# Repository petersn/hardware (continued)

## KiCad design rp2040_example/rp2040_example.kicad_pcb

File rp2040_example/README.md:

RP2040 example board
====================

This board is enormously cribbed from the RP2040 example board, as described here: https://datasheets.raspberrypi.com/rp2040/hardware-design-with-rp2040.pdf

(The corresponding KiCad files are here: https://datasheets.raspberrypi.com/rp2040/Minimal-KiCAD.zip)

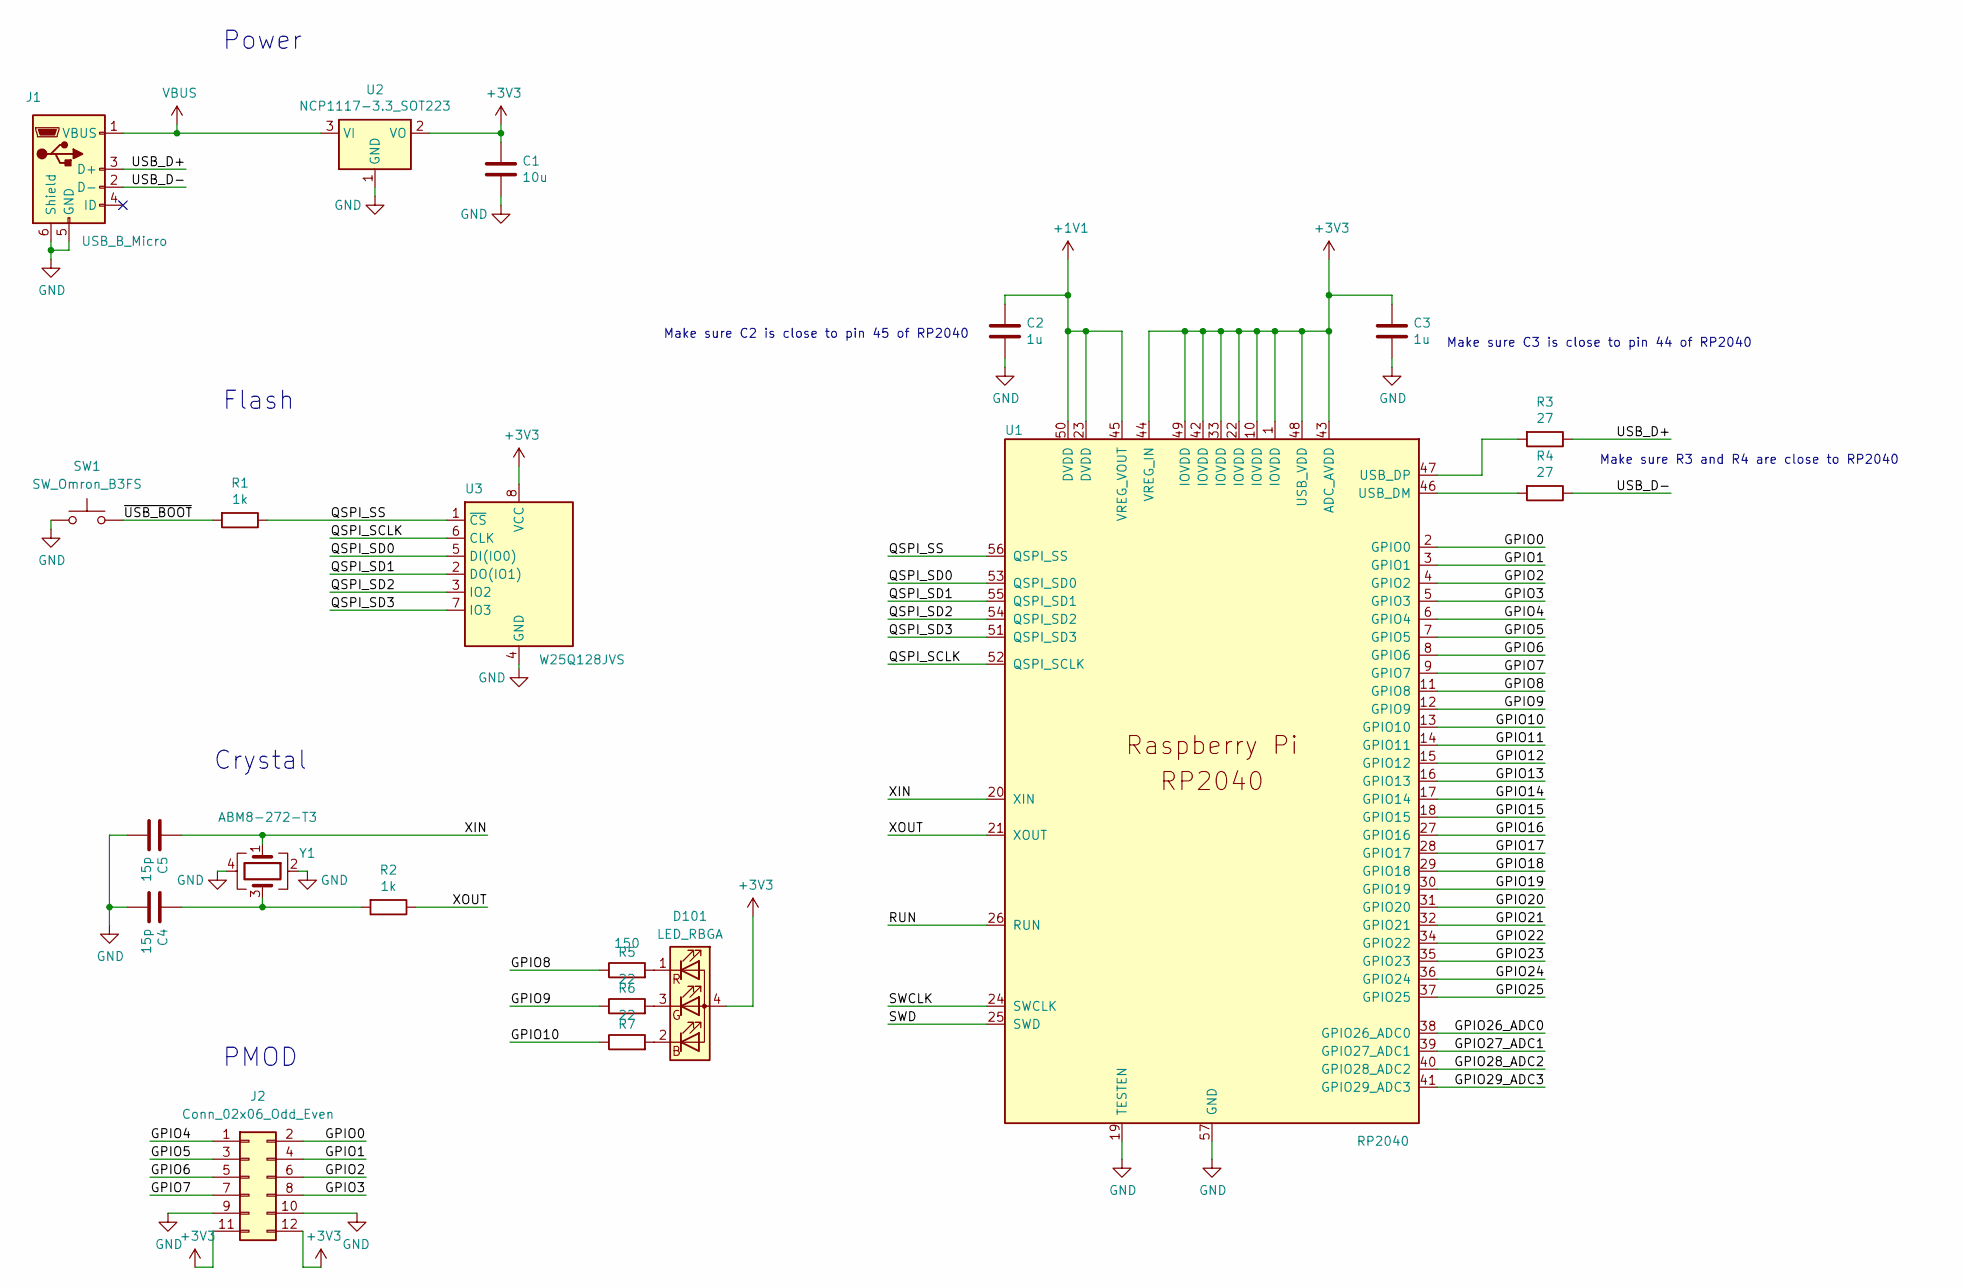
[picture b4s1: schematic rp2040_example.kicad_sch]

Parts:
C1: 10u; C_0805_2012Metric
C2, C3: 1u; C_0402_1005Metric
C4, C5: 15p; C_0402_1005Metric
D101: LED_RBGA; LED_LiteOn_LTST-C19HE1WT
J1: USB_B_Micro; USB_Micro-B_Amphenol_10103594-0001LF_Horizontal
J2: Conn_02x06_Odd_Even; PinHeader_2x06_P2.54mm_Vertical
R1, R2: 1k; R_0402_1005Metric
R3, R4: 27; R_0402_1005Metric
R5: 150; R_0402_1005Metric
R6, R7: 22; R_0402_1005Metric
SW1: SW_Omron_B3FS; SW_PUSH_6mm
U1: RP2040; QFN-56-1EP_7x7mm_P0.4mm_EP4x4mm_ThermalVias
U2: NCP1117-3.3_SOT223; SOT-223-3_TabPin2
U3: W25Q128JVS; SOIC-8_5.23x5.23mm_P1.27mm
Y1: ABM8-272-T3; Crystal_SMD_3225-4Pin_3.2x2.5mm

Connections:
+1V1: C2.1, U1.23 (DVDD), U1.45 (VREG_VOUT), U1.50 (DVDD)
+3V3: C1.1, C3.1, D101.4 (A), J2.11, J2.12, U1.1 (IOVDD), U1.10 (IOVDD), U1.22 (IOVDD), U1.33 (IOVDD), U1.42 (IOVDD), U1.43 (ADC_AVDD), U1.44 (VREG_IN), U1.48 (USB_VDD), U1.49 (IOVDD), U2.2 (VO), U3.8 (VCC)
/GPIO0: J2.2, U1.2 (GPIO0)
/GPIO1: J2.4, U1.3 (GPIO1)
/GPIO2: J2.6, U1.4 (GPIO2)
/GPIO3: J2.8, U1.5 (GPIO3)
/GPIO4: J2.1, U1.6 (GPIO4)
/GPIO5: J2.3, U1.7 (GPIO5)
/GPIO6: J2.5, U1.8 (GPIO6)
/GPIO7: J2.7, U1.9 (GPIO7)
/GPIO8: R5.1, U1.11 (GPIO8)
/GPIO9: R6.1, U1.12 (GPIO9)
/GPIO10: R7.1, U1.13 (GPIO10)
/GPIO11: U1.14 (GPIO11)
/GPIO12: U1.15 (GPIO12)
/GPIO13: U1.16 (GPIO13)
/GPIO14: U1.17 (GPIO14)
/GPIO15: U1.18 (GPIO15)
/GPIO16: U1.27 (GPIO16)
/GPIO17: U1.28 (GPIO17)
/GPIO18: U1.29 (GPIO18)
/GPIO19: U1.30 (GPIO19)
/GPIO20: U1.31 (GPIO20)
/GPIO21: U1.32 (GPIO21)
/GPIO22: U1.34 (GPIO22)
/GPIO23: U1.35 (GPIO23)
/GPIO24: U1.36 (GPIO24)
/GPIO25: U1.37 (GPIO25)
/GPIO26_ADC0: U1.38 (GPIO26_ADC0)
/GPIO27_ADC1: U1.39 (GPIO27_ADC1)
/GPIO28_ADC2: U1.40 (GPIO28_ADC2)
/GPIO29_ADC3: U1.41 (GPIO29_ADC3)
/QSPI_SCLK: U1.52 (QSPI_SCLK), U3.6 (CLK)
/QSPI_SD0: U1.53 (QSPI_SD0), U3.5 (DI(IO0))
/QSPI_SD1: U1.55 (QSPI_SD1), U3.2 (DO(IO1))
/QSPI_SD2: U1.54 (QSPI_SD2), U3.3 (IO2)
/QSPI_SD3: U1.51 (QSPI_SD3), U3.7 (IO3)
/QSPI_SS: R1.1, U1.56 (QSPI_SS), U3.1 (~CS)
/RUN: U1.26 (RUN)
/SWCLK: U1.24 (SWCLK)
/SWD: U1.25 (SWD)
/USB_D+: J1.3 (D+), R3.1
/USB_D-: J1.2 (D-), R4.1
/XIN: C5.1, U1.20 (XIN), Y1.1
/XOUT: R2.1, U1.21 (XOUT)
/~USB_BOOT: R1.2, SW1.2
GND: C1.2, C2.2, C3.2, C4.2, C5.2, J1.5 (GND), J1.6 (Shield), J2.9, J2.10, SW1.1, U1.19 (TESTEN), U1.57 (GND), U2.1 (GND), U3.4 (GND), Y1.2, Y1.4
unnamed: C4.1, R2.2, Y1.3
unnamed: D101.2 (BK), R7.2
unnamed: D101.3 (GK), R6.2
unnamed: D101.1 (RK), R5.2
unnamed: R4.2, U1.46 (USB_DM)
unnamed: R3.2, U1.47 (USB_DP)
VBUS: J1.1 (VBUS), U2.3 (VI)

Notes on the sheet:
Crystal
Make sure C2 is close to pin 45 of RP2040
Make sure R3 and R4 are close to RP2040
Flash
Power
PMOD
Make sure C3 is close to pin 44 of RP2040

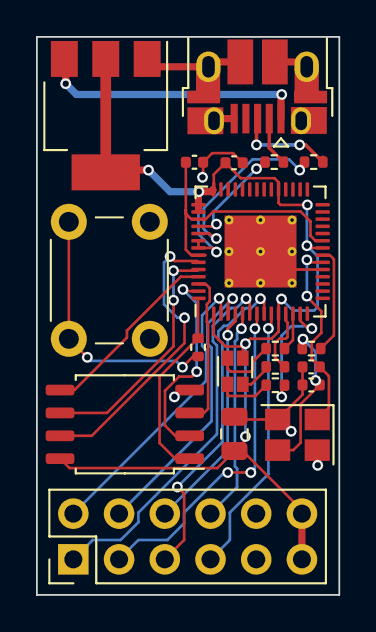
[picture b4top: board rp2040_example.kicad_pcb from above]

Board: 2 copper layers, 16.8 x 31.0 mm, 20 parts (0 on the bottom side), 32 nets.

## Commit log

2024-03-19 Adding rp2040_example board, based on their example
2024-03-19 Adding image
2024-03-19 Oops, forgot exclamation point
2024-03-19 Rotate board image
2024-04-02 Starting on handheld
2024-04-02 Change reference on RP2040 example
2024-04-02 More changes
2024-04-03 More nonsense
2024-04-05 Sent off a version
2024-09-22 Add artix7
2024-09-23 Final version before switching from XC7A35T-xFTG256 to -xCSG325
2024-09-23 JLCPCB uploads
2024-09-25 Battery stay on stuff
2024-09-26 ice40
2024-09-26 I don't know what these changes are
2024-09-26 Nonsense
2024-10-20 Basic blinky code
